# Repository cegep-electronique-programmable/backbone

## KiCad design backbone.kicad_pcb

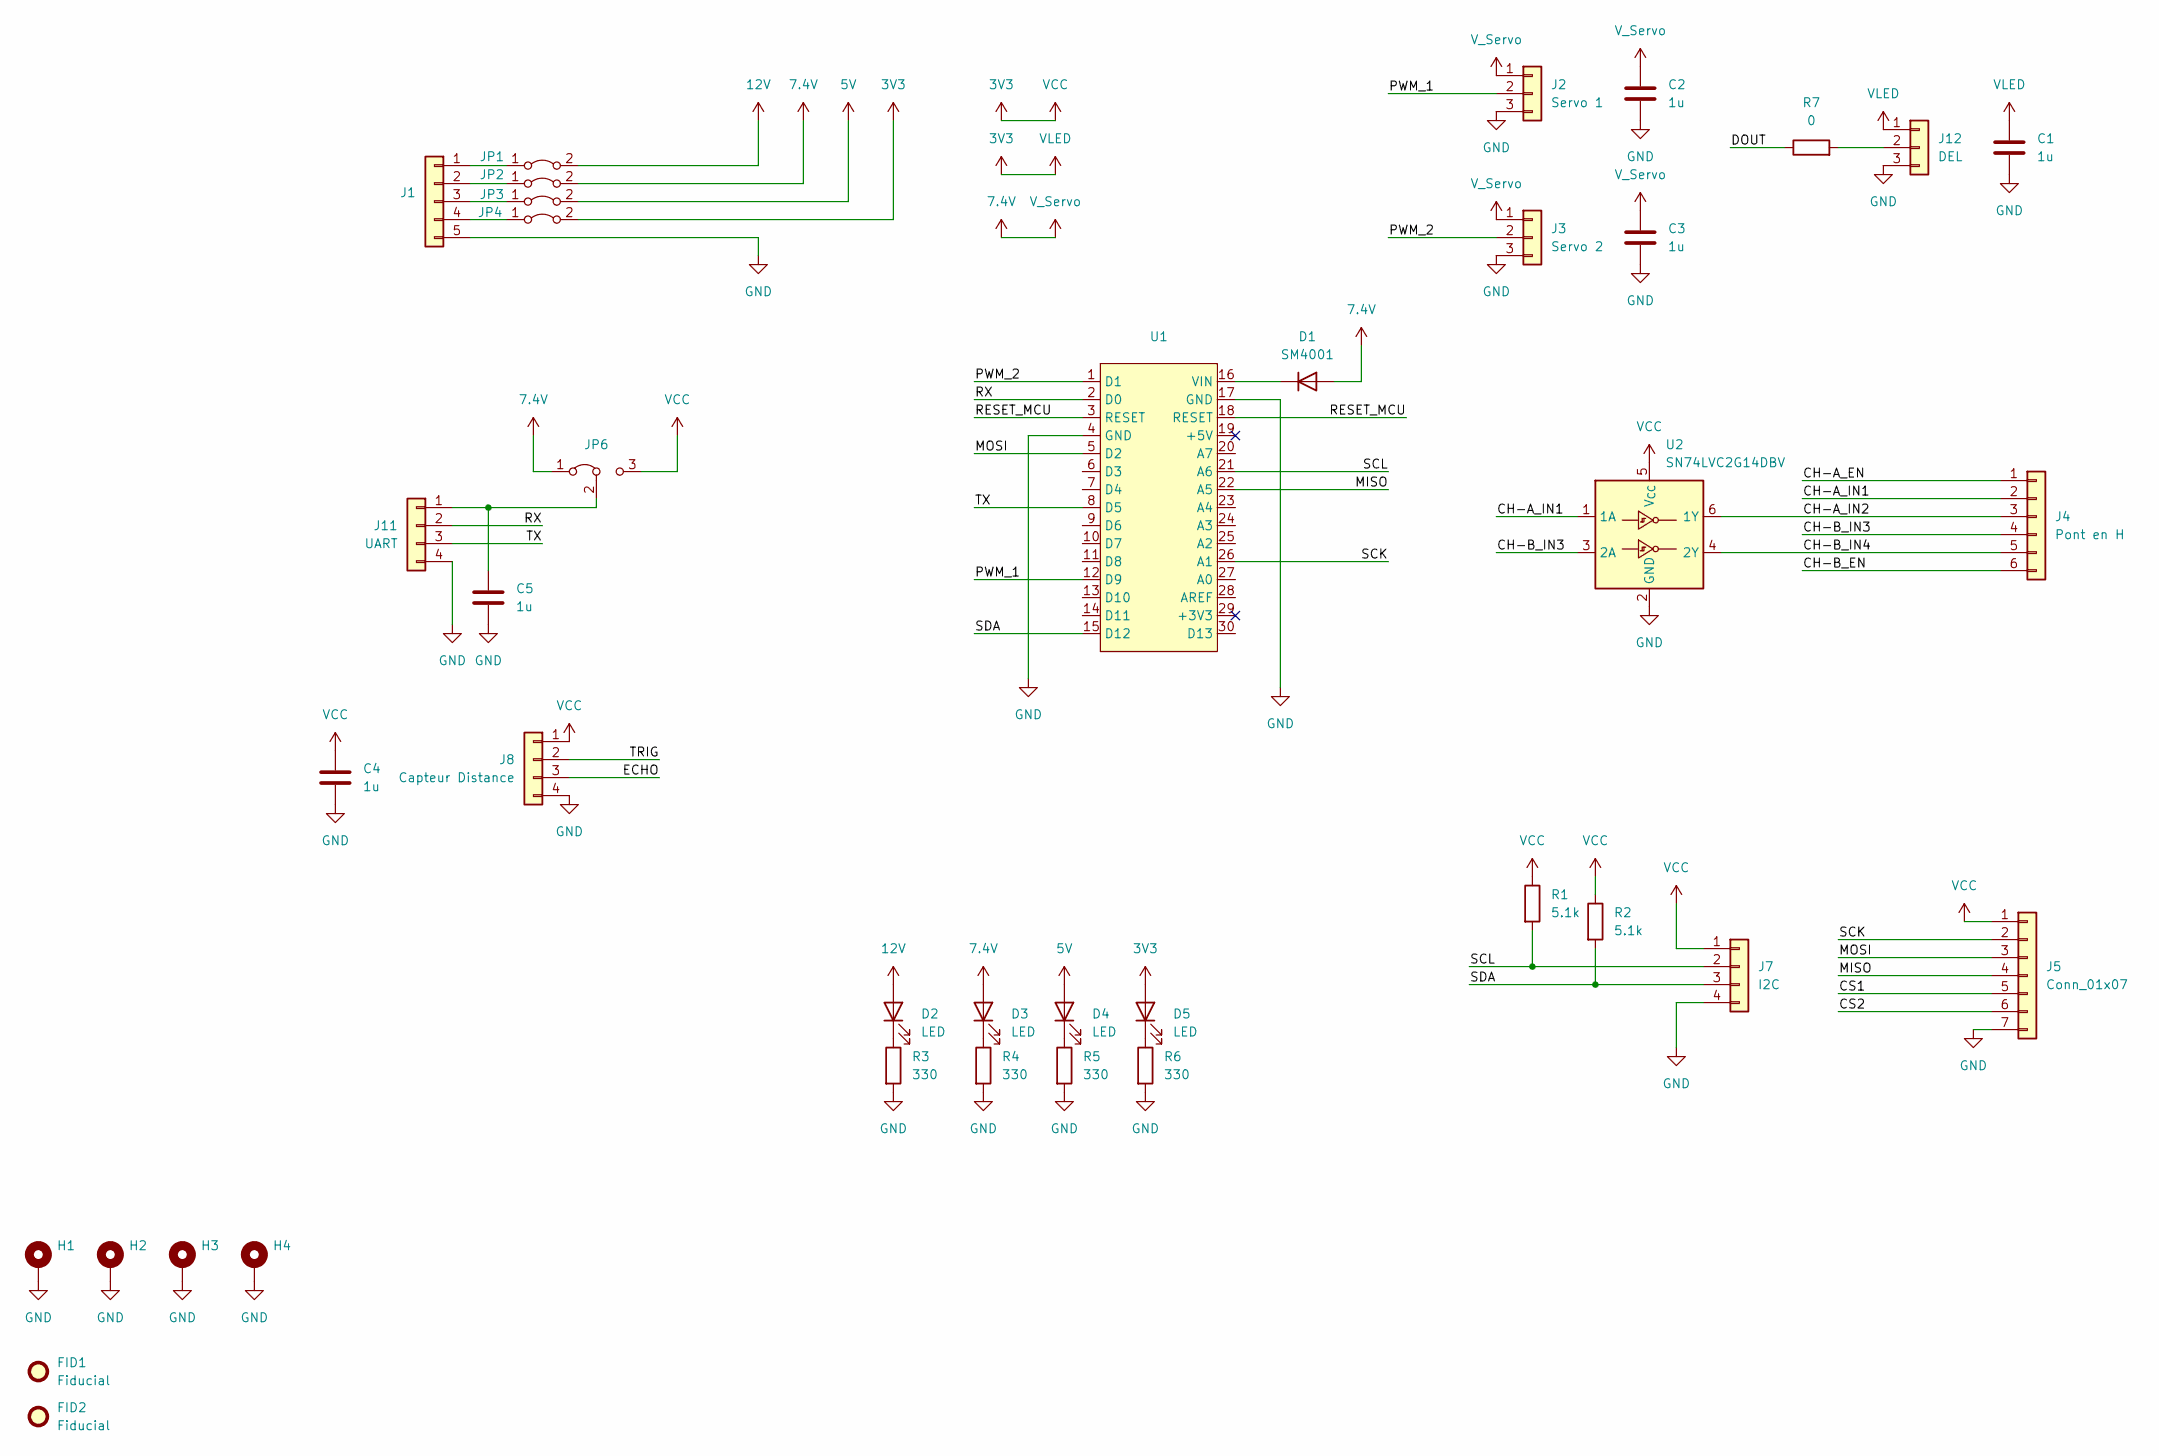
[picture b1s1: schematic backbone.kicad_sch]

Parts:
C1, C2, C3, C4, C5: 1u; C_0805_2012Metric_Pad1.18x1.45mm_HandSolder
D1: SM4001; D_MELF
D2, D3, D4, D5: LED; LED_0805_2012Metric_Pad1.15x1.40mm_HandSolder
FID1, FID2: Fiducial; Fiducial_1.5mm_Mask4.5mm
H1, H2, H3, H4: MountingHole_Pad; MountingHole_3.2mm_M3_DIN965_Pad
J1: Conn_01x05; Carte_alimentation
J2: Servo 1; PinHeader_1x03_P2.54mm_Vertical
J3: Servo 2; PinHeader_1x03_P2.54mm_Vertical
J4: Pont en H; PinHeader_1x06_P2.54mm_Vertical
J5: Conn_01x07; PinHeader_1x07_P2.54mm_Vertical
J7: I2C; PinHeader_1x04_P2.54mm_Vertical
J8: Capteur Distance; PinHeader_1x04_P2.54mm_Vertical
J11: UART; PinHeader_1x04_P2.54mm_Vertical
J12: DEL; PinHeader_1x03_P2.54mm_Vertical
JP1, JP2, JP3, JP4: Jumper_2_Bridged; PinHeader_1x02_P2.54mm_Vertical
JP6: Jumper_3_Bridged12; PinHeader_1x03_P2.54mm_Vertical
R1, R2: 5.1k; R_0805_2012Metric_Pad1.20x1.40mm_HandSolder
R3, R4, R5, R6: 330; R_0805_2012Metric_Pad1.20x1.40mm_HandSolder
R7: 0; R_0805_2012Metric_Pad1.20x1.40mm_HandSolder
U1: Arduino_Nano_WithMountingHoles
U2: SN74LVC2G14DBV; SOT-23-6

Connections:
3V3: C1.1, C4.1, D5.2 (A), J5.1, J7.1, J8.1, J12.1, JP4.2 (B), JP6.3 (B), R1.1, R2.1, U2.5 (V_{CC})
5V: D4.2 (A), JP3.2 (B)
7.4V: C2.1, C3.1, D1.2 (A), D3.2 (A), J2.1, J3.1, JP2.2 (B), JP6.1 (A)
12V: D2.2 (A), JP1.2 (B)
/CH-A_EN: J4.1
/CH-A_IN1: J4.2, U2.1 (1A)
/CH-A_IN2: J4.3, U2.6 (1Y)
/CH-B_EN: J4.6
/CH-B_IN3: J4.4, U2.3 (2A)
/CH-B_IN4: J4.5, U2.4 (2Y)
/CS1: J5.5
/CS2: J5.6
/DOUT: R7.1
/ECHO: J8.3
/MISO: J5.4, U1.22 (A5)
/MOSI: J5.3, U1.5 (D2)
/PWM_1: J2.2, U1.12 (D9)
/PWM_2: J3.2, U1.1 (D1)
/RESET_MCU: U1.3 (RESET), U1.18 (RESET)
/RX: J11.2, U1.2 (D0)
/SCK: J5.2, U1.26 (A1)
/SCL: J7.2, R1.2, U1.21 (A6)
/SDA: J7.3, R2.2, U1.15 (D12)
/TRIG: J8.2
/TX: J11.3, U1.8 (D5)
GND: C1.2, C2.2, C3.2, C4.2, C5.2, H1.1, H2.1, H3.1, H4.1, J1.5, J2.3, J3.3, J5.7, J7.4, J8.4, J11.4, J12.3, R3.2, R4.2, R5.2, R6.2, U1.4 (GND), U1.17 (GND), U2.2 (GND)
unnamed: D1.1 (K), U1.16 (VIN)
unnamed: D2.1 (K), R3.1
unnamed: D3.1 (K), R4.1
unnamed: D4.1 (K), R5.1
unnamed: D5.1 (K), R6.1
unnamed: J1.1, JP1.1 (A)
unnamed: J1.2, JP2.1 (A)
unnamed: J1.3, JP3.1 (A)
unnamed: J1.4, JP4.1 (A)
unnamed: C5.1, J11.1, JP6.2 (C)
unnamed: J12.2, R7.2

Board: 2 copper layers, 39 parts (0 on the bottom side), 30 nets, no tracks yet.
